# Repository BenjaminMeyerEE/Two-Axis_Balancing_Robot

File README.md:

# Two-Axis Balancing Robot

A robot that balances in pitch and roll. The two axes use different hardware: pitch
runs a brushless motor through a VESC over CAN, roll runs a brushed motor through an
H-bridge on a custom power board. Both close around an STM32G474 and an ICM-42688-P
IMU on a custom carrier board. Two custom 4-layer boards, designed in KiCad.

<!-- TODO
     - mechanical: CAD screenshots once the design is finished
     - the Simulink model and the LQR weight-selection model, once cleaned up
     - fp-lib-table on both boards points at C:/Users/brmey/Downloads, so footprint
       libraries won't resolve on another machine
     - the carrier render uses a Nucleo-64 F401 STEP as a stand-in; same form factor
       as the G474RE but the silkscreen says F411 if you look closely
     images are generated, see docs/regenerate-images.md
-->

## Specifications

| Parameter | Value |
|---|---|
| Axes | Pitch and roll, separate drive hardware |
| Controller | STM32G474RET6 (Nucleo-G474RE on the carrier board) |
| IMU | ICM-42688-P over SPI, both interrupt lines broken out |
| Pitch drive | Brushless motor via VESC, commanded over CAN |
| Pitch feedback | TLE5012 magnetic encoder, SPI to the VESC |
| Roll drive | Brushed motor via TB6612FNG dual H-bridge |
| Roll feedback | Quadrature encoder into the carrier board |
| Battery | 3S LiPo, 11.1 V nominal |
| Carrier board | 101.6 × 92.9 mm, 4-layer |
| Power board | 50.0 × 42.9 mm, 4-layer |

## Status

Both custom PCBs are designed and the electrical architecture is laid out. Mechanical
design is partly finished.

I simulated the pitch axis in Simulink first, and that's what pushed me away from PID
and toward LQR. Wheel position and tilt are coupled through the dynamics, so tuning
them as separate loops meant the two kept fighting each other. Full state feedback
made more sense than trying to manage that interaction by hand.

What I'm working on now is the model itself: deriving the equations of motion with
Lagrangian mechanics, linearizing about the upright equilibrium, and designing a
discrete-time LQR with Bryson's rule setting the cost weights. That work is all in
MATLAB.

## Repository layout

| Path | Contents |
|---|---|
| `hardware/two_axis_balancing_carrier/` | Carrier board KiCad project |
| `hardware/two_axis_balancing_power/` | Power board KiCad project |
| `docs/` | Architecture diagram, board renders, layer plots |

## Hardware

Both boards are 4-layer. Every copper layer below is plotted from the top and
unmirrored, so features line up between layers.

### Carrier board

101.6 × 92.9 mm. Holds the Nucleo-G474RE and everything the control loop reads.

| | |
|---|---|
|  |  |

The ICM-42688-P is on SPI (`CS`, `SCLK`, `SDI`, `SDO`) with `INT1` and `INT2` brought
out, so the loop can run off data-ready rather than polling. An SN65HVD230 with 120 Ω
termination puts the board on the CAN bus to the VESC. A MIC5219-3.3 makes the 3.3 V
rail from the 5 V coming off the power board.

Roll encoder channels come in here on `ENC_A` / `ENC_B`. Motor commands (`AIN1`,
`AIN2`, `PWMA`, `STBY`) and the battery signals go back to the power board over a 2×5
IDC ribbon. There are 13 test points, and the SPI, UART, encoder and rail pads are all
labelled on the silkscreen for bring-up.

| `F.Cu` | `In1.Cu` |
|---|---|
|  |  |

| `In2.Cu` | `B.Cu` |
|---|---|
|  |  |

### Power board

50.0 × 42.9 mm. Takes the battery in and handles everything that touches VBAT.

| | |
|---|---|
|  |  |

Battery comes in on an XT60, behind a 3 A fuse, an AO3401A P-channel MOSFET for
reverse polarity, and a 10 V zener. An RPL-1.0-R module makes the 5 V rail and reports
`Buck_PG` back to the MCU. A TB6612FNG dual H-bridge drives the roll motor on
`MOTOR_P` / `MOTOR_N`.

Battery monitoring is done on this board rather than in firmware. A divider gives
`BAT_LEV`, an LM393 compares it against `BAT_REF`, and `BAT_LOW` goes back to the
carrier board. The MCU sees both the raw level and a latched low flag.

| `F.Cu` | `In1.Cu` |
|---|---|
|  |  |

| `In2.Cu` | `B.Cu` |
|---|---|
|  |  |

### Connectors

| Board | Ref | Connector | Carries |
|---|---|---|---|
| Power | `J1` | XT60 | 3S battery in |
| Power | `J3` | JST XH, 2-pin | Roll motor out (`MOTOR_P` / `MOTOR_N`) |
| Power | `J2` | IDC 2×5 | To the carrier board |
| Carrier | `J5` | IDC 2×5 | To the power board |
| Carrier | `J2` | JST XH, 4-pin | Roll encoder (`ENC_A`, `ENC_B`, 5 V, GND) |
| Carrier | `J1` | JST GH, 3-pin | CAN to the VESC (`CANH`, `CANL`, GND) |

The 2×5 ribbon is the only link between the two boards. It carries the 5 V rail and
ground, the four TB6612FNG control lines (`AIN1`, `AIN2`, `PWMA`, `STBY`) and the two
battery monitoring signals (`BAT_LEV`, `BAT_LOW`). VBAT never reaches the carrier
board, which only ever sees 5 V.

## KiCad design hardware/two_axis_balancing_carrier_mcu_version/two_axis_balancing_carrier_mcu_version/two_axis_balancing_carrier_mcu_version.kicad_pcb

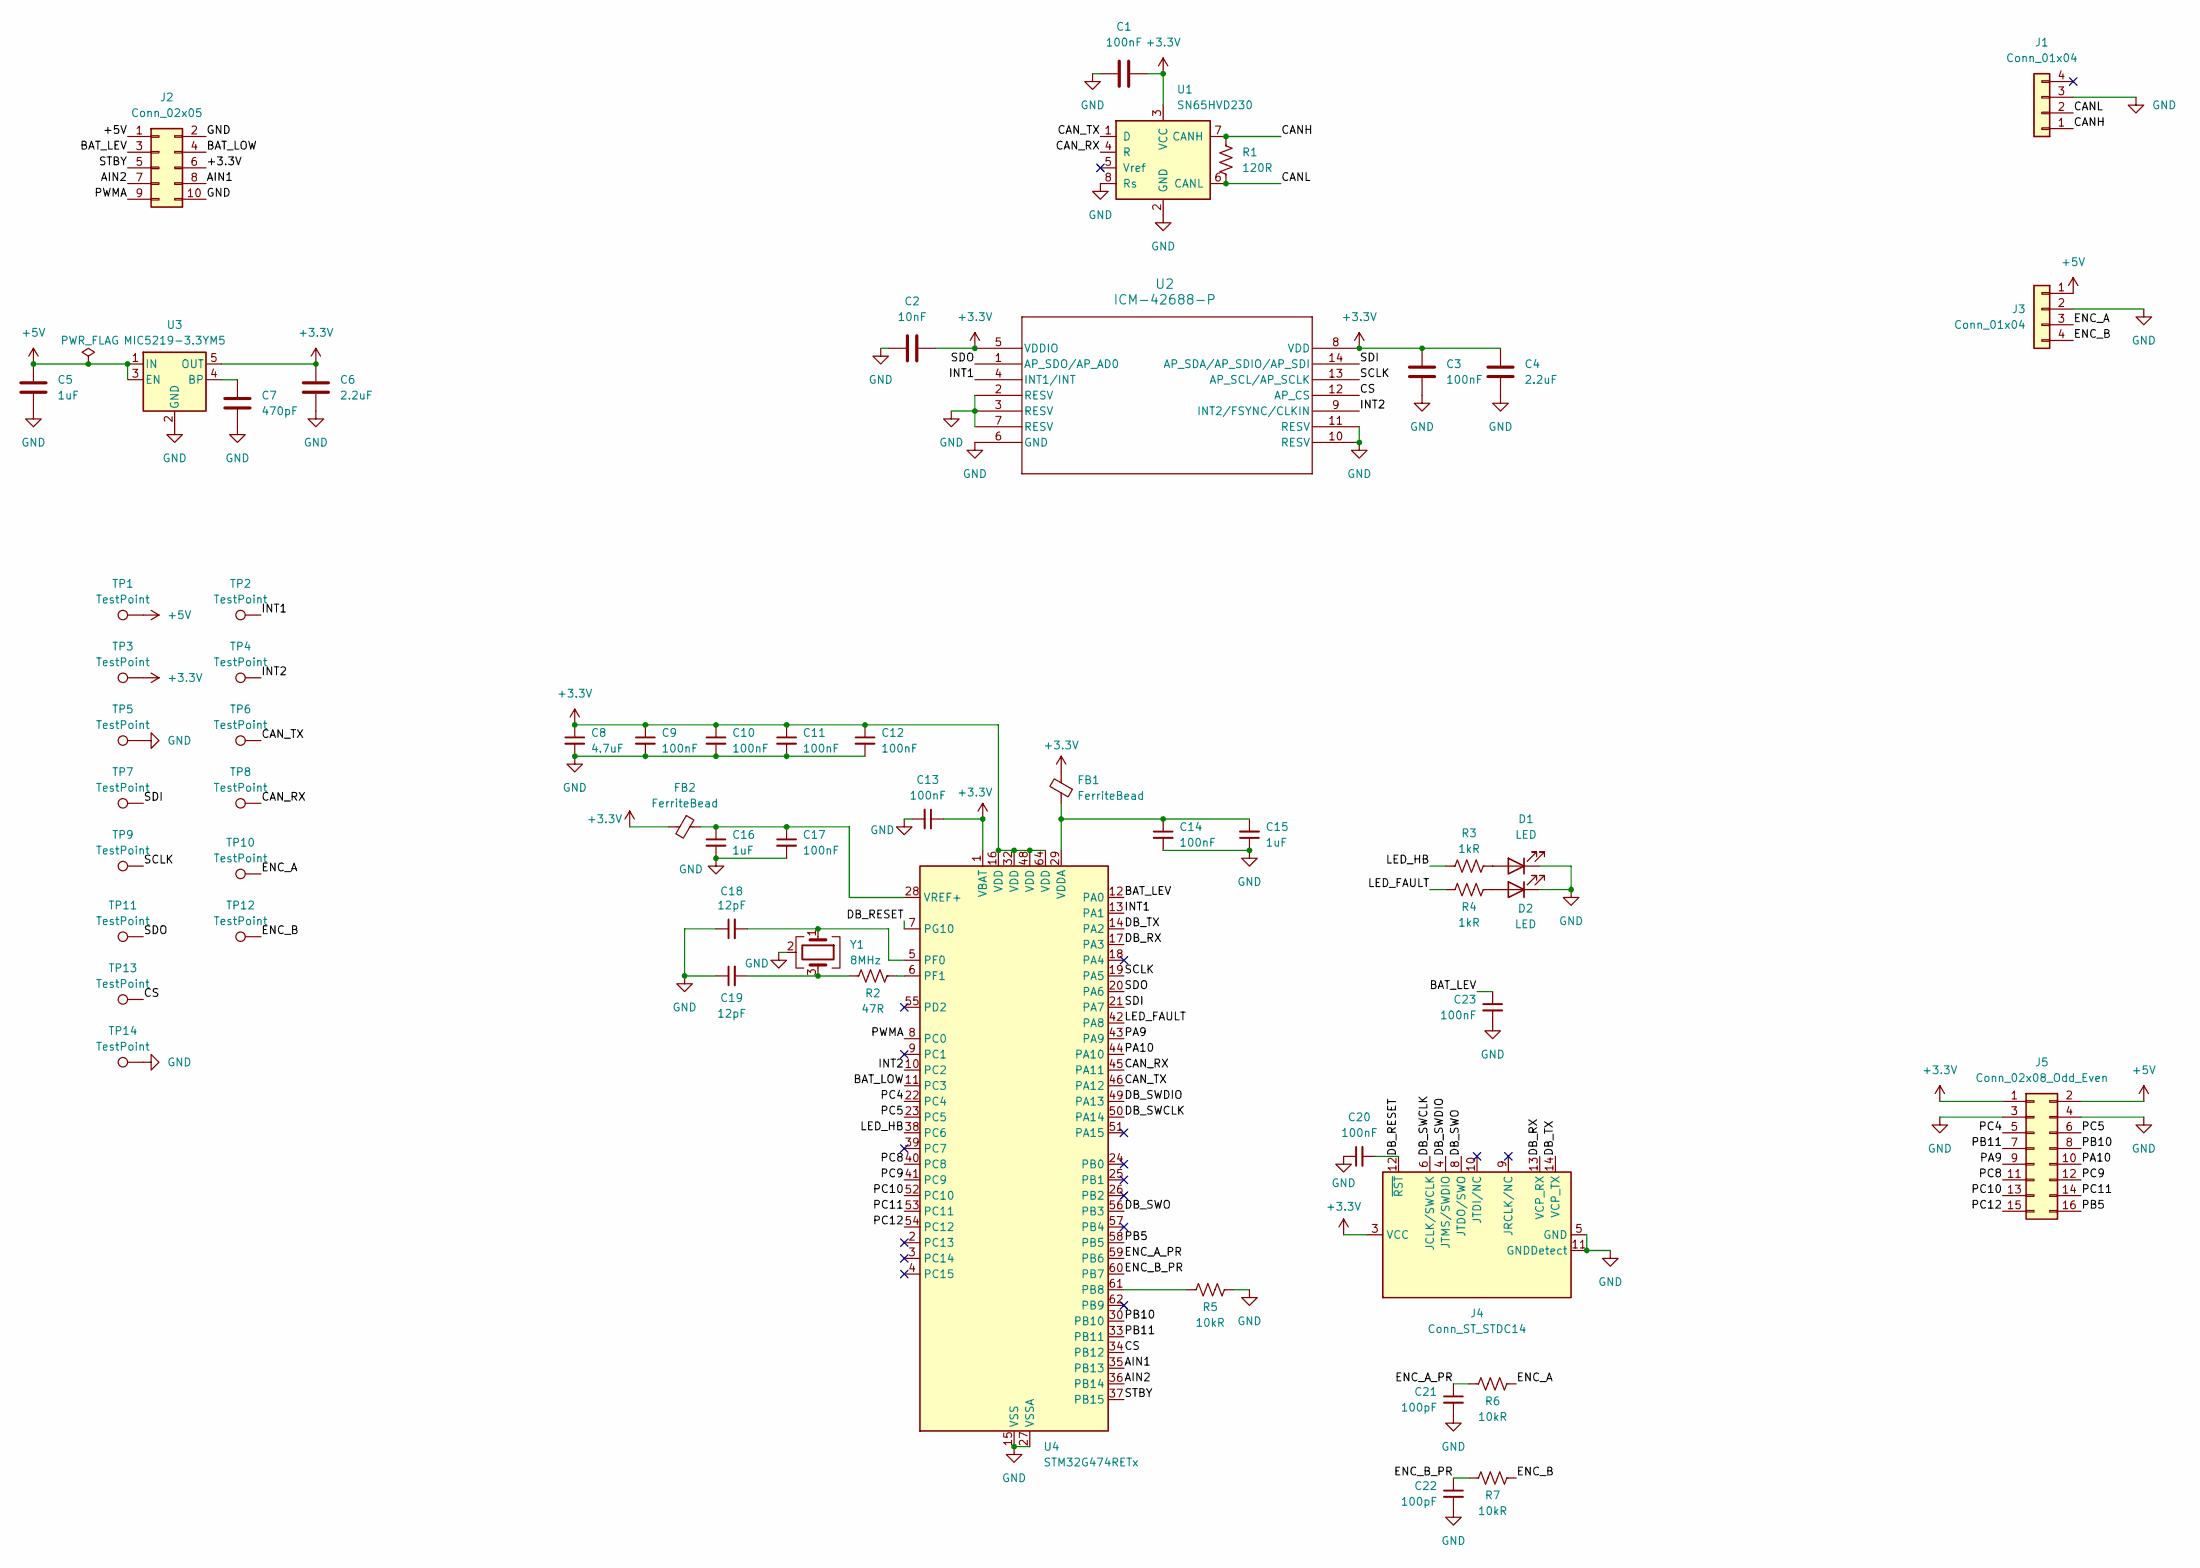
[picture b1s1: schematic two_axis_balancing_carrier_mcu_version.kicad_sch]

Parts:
C1, C3, C9, C10, C11, C12, C13, C14, C17, C20, C23: 100nF; C_0603_1608Metric
C2: 10nF; C_0603_1608Metric
C4, C6: 2.2uF; C_0805_2012Metric
C5: 1uF; C_0603_1608Metric
C7: 470pF; C_0603_1608Metric
C8: 4.7uF; C_0805_2012Metric
C15, C16: 1uF; C_0805_2012Metric
C18, C19: 12pF; C_0603_1608Metric
C21, C22: 100pF; C_0603_1608Metric
D1, D2: LED; LED_0603_1608Metric
FB1, FB2: FerriteBead; C_0603_1608Metric
J1: Conn_01x04; JST_GH_BM04B-GHS-TBT_1x04-1MP_P1.25mm_Vertical
J2: Conn_02x05; IDC-Header_2x05_P2.54mm_Vertical
J3: Conn_01x04; JST_XH_B4B-XH-A_1x04_P2.50mm_Vertical
J4: Conn_ST_STDC14; PinHeader_2x07_P1.27mm_Vertical
J5: Conn_02x08_Odd_Even; PinHeader_2x08_P2.54mm_Vertical
R1: 120R; R_0603_1608Metric
R2: 47R; R_0603_1608Metric
R3, R4: 1kR; R_0603_1608Metric
R5, R6, R7: 10kR; R_0603_1608Metric
TP1, TP2, TP3, TP4, TP6, TP7, TP8, TP9, TP10, TP11, TP12, TP13: TestPoint; TestPoint_Pad_D1.0mm
TP5, TP14: TestPoint; TestPoint_Keystone_5015_Micro_Mini
U1: SN65HVD230; SOIC-8_3.9x4.9mm_P1.27mm
U2: ICM-42688-P; LGA14_2P5X3X0P91_TDK
U3: MIC5219-3.3YM5; SOT-23-5
U4: STM32G474RETx; LQFP-64_10x10mm_P0.5mm
Y1: 8MHz; Crystal_SMD_3225-4Pin_3.2x2.5mm

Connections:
+3.3V: C1.1, C2.2, C3.1, C4.1, C6.1, C8.1, C9.1, C10.1, C11.1, C12.1, C13.1, FB1.2, FB2.2, J2.6, J4.3 (VCC), J5.1, TP3.1 (1_1), U1.3 (VCC), U2.5 (VDDIO), U2.8 (VDD), U3.5 (OUT), U4.1 (VBAT), U4.16 (VDD), U4.32 (VDD), U4.48 (VDD), U4.64 (VDD)
+5V: C5.1, J2.1, J3.1, J5.2, TP1.1 (1_1), U3.1 (IN), U3.3 (EN)
/AIN1: J2.8, U4.35 (PB13)
/AIN2: J2.7, U4.36 (PB14)
/BAT_LEV: C23.1, J2.3, U4.12 (PA0)
/BAT_LOW: J2.4, U4.11 (PC3)
/CANH: J1.1, R1.1, U1.7 (CANH)
/CANL: J1.2, R1.2, U1.6 (CANL)
/CAN_RX: TP8.1 (1_1), U1.4 (R), U4.45 (PA11)
/CAN_TX: TP6.1 (1_1), U1.1 (D), U4.46 (PA12)
/CS: TP13.1 (1_1), U2.12 (AP_CS), U4.34 (PB12)
/DB_RESET: C20.2, J4.12 (~RST), U4.7 (PG10)
/DB_RX: J4.13 (VCP_RX), U4.17 (PA3)
/DB_SWCLK: J4.6 (JCLK/SWCLK), U4.50 (PA14)
/DB_SWDIO: J4.4 (JTMS/SWDIO), U4.49 (PA13)
/DB_SWO: J4.8 (JTDO/SWO), U4.56 (PB3)
/DB_TX: J4.14 (VCP_TX), U4.14 (PA2)
/ENC_A: J3.3, R6.2, TP10.1 (1_1)
/ENC_A_PR: C21.1, R6.1, U4.59 (PB6)
/ENC_B: J3.4, R7.2, TP12.1 (1_1)
/ENC_B_PR: C22.1, R7.1, U4.60 (PB7)
/INT1: TP2.1 (1_1), U2.4 (INT1/INT), U4.13 (PA1)
/INT2: TP4.1 (1_1), U2.9 (INT2/FSYNC/CLKIN), U4.10 (PC2)
/LED_FAULT: R4.1, U4.42 (PA8)
/LED_HB: R3.1, U4.38 (PC6)
/PA9: J5.9, U4.43 (PA9)
/PA10: J5.10, U4.44 (PA10)
/PB5: J5.16, U4.58 (PB5)
/PB10: J5.8, U4.30 (PB10)
/PB11: J5.7, U4.33 (PB11)
/PC4: J5.5, U4.22 (PC4)
/PC5: J5.6, U4.23 (PC5)
/PC8: J5.11, U4.40 (PC8)
/PC9: J5.12, U4.41 (PC9)
/PC10: J5.13, U4.52 (PC10)
/PC11: J5.14, U4.53 (PC11)
/PC12: J5.15, U4.54 (PC12)
/PWMA: J2.9, U4.8 (PC0)
/SCLK: TP9.1 (1_1), U2.13 (AP_SCL/AP_SCLK), U4.19 (PA5)
/SDI: TP7.1 (1_1), U2.14 (AP_SDA/AP_SDIO/AP_SDI), U4.21 (PA7)
/SDO: TP11.1 (1_1), U2.1 (AP_SDO/AP_AD0), U4.20 (PA6)
/STBY: J2.5, U4.37 (PB15)
GND: C1.2, C2.1, C3.2, C4.2, C5.2, C6.2, C7.2, C8.2, C9.2, C10.2, C11.2, C12.2, C13.2, C14.2, C15.1, C16.2, C17.2, C18.1, C19.1, C20.1, C21.2, C22.2, C23.2, D1.1 (K), D2.1 (K), J1.3, J2.2, J2.10, J3.2, J4.5 (GND), J4.7 (GND), J4.11 (GNDDetect), J5.3, J5.4, R5.2, TP5.1 (1_1), TP14.1 (1_1), U1.2 (GND), U1.8 (Rs), U2.2 (RESV), U2.3 (RESV), U2.6 (GND), U2.7 (RESV), U2.10 (RESV), U2.11 (RESV), U3.2 (GND), U4.15 (VSS), U4.27 (VSSA), U4.31 (VSS), U4.47 (VSS), U4.63 (VSS), Y1.2 (G), Y1.4 (G)
unnamed: C19.2, R2.1, Y1.3
unnamed: D1.2 (A), R3.2
unnamed: D2.2 (A), R4.2
unnamed: C7.1, U3.4 (BP)
unnamed: R5.1, U4.61 (PB8)
unnamed: C18.2, U4.5 (PF0), Y1.1
unnamed: R2.2, U4.6 (PF1)
unnamed: C14.1, C15.2, FB1.1, U4.29 (VDDA)
unnamed: C16.1, C17.1, FB2.1, U4.28 (VREF+)

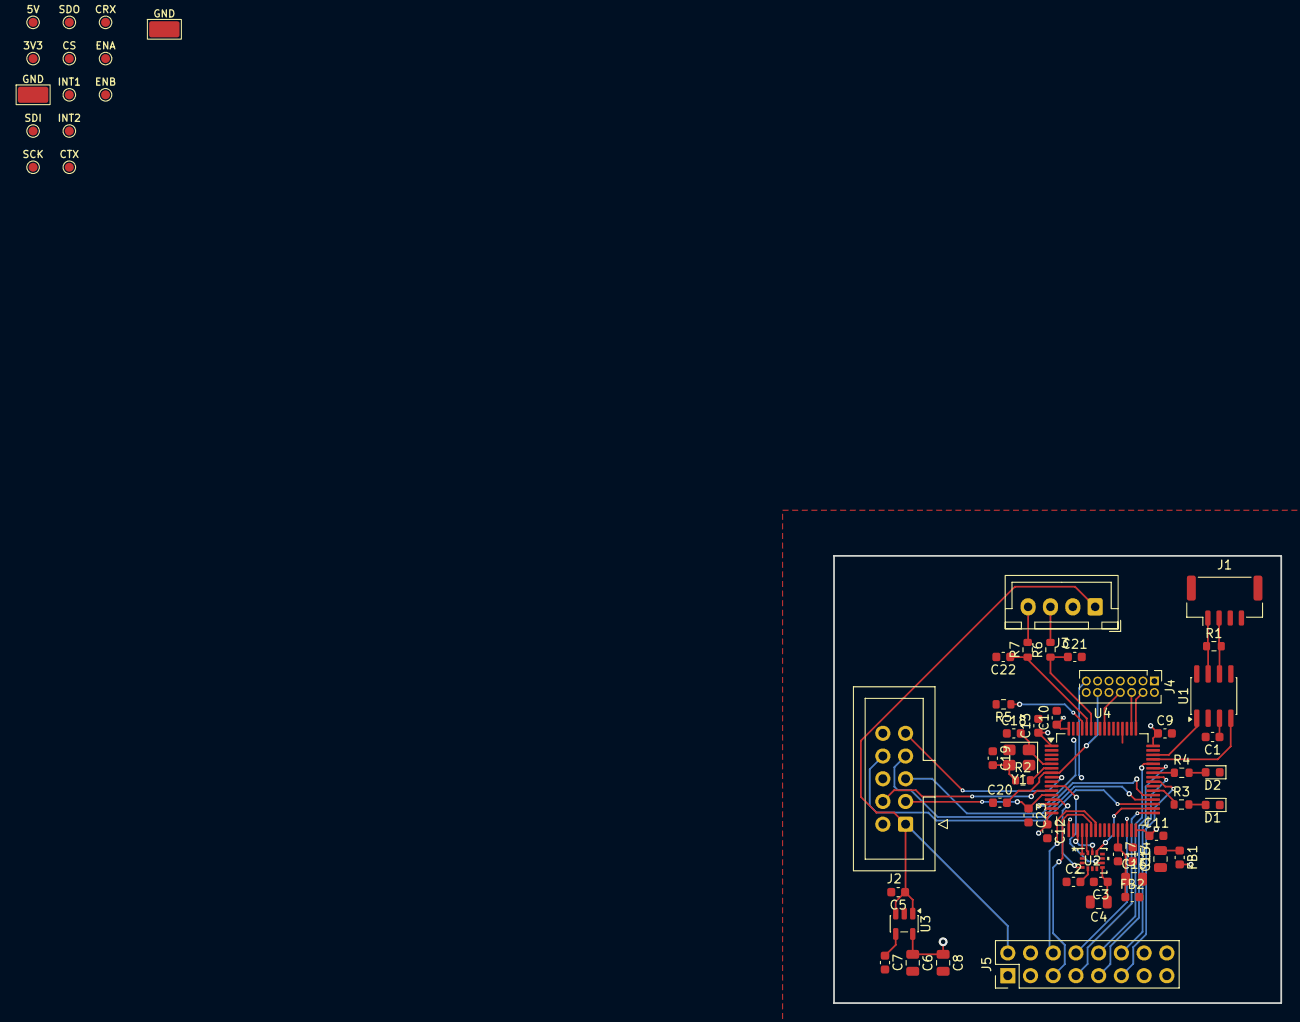
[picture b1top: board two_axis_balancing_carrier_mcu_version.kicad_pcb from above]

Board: 4 copper layers, 50.0 x 50.0 mm, 58 parts (0 on the bottom side), 52 nets.

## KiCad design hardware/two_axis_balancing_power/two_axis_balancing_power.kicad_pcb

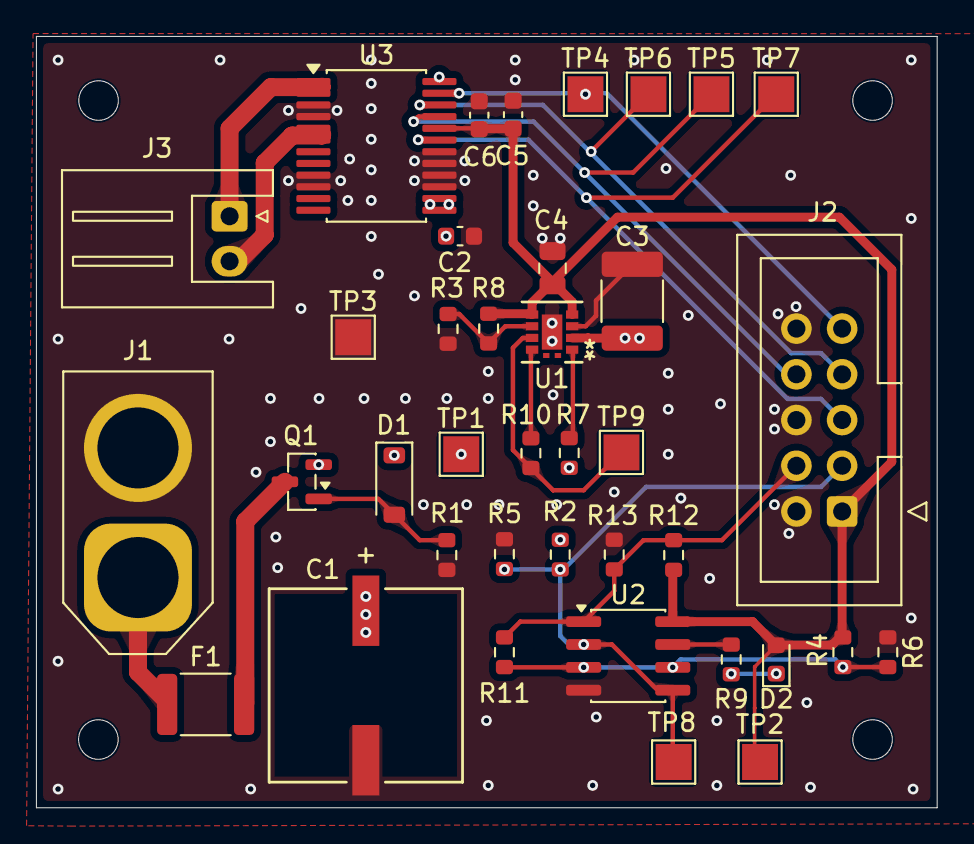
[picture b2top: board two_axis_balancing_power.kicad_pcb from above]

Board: 4 copper layers, 50.0 x 42.9 mm, 38 parts (0 on the bottom side), 21 nets.

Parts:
C1: 470uF; PCAP_10x10-ELECT_NCA
C2, C6: 100nF; C_0603_1608Metric
C3: 20uF; C_1812_4532Metric
C4: 22uF; C_0805_2012Metric
C5: 10uF; C_0603_1608Metric
D1: 10V; D_SOD-123
D2: LED; LED_0603_1608Metric
F1: 3A; Fuse_1812_4532Metric
J1: Conn_01x02; AMASS_XT60-M_1x02_P7.20mm_Vertical
J2: Conn_02x05; IDC-Header_2x05_P2.54mm_Vertical
J3: Conn_01x02; JST_XH_S2B-XH-A_1x02_P2.50mm_Horizontal
Q1: AO3401A; SOT-23
R1, R4, R5, R12: 10kR; R_0603_1608Metric
R2: 47kR; R_0603_1608Metric
R3, R11: 220kR; R_0603_1608Metric
R6: 5.9kR; R_0603_1608Metric
R7, R10: 100kR; R_0603_1608Metric
R8: 1613kR; R_0603_1608Metric
R9: 470R; R_0603_1608Metric
R13: 15kR; R_0603_1608Metric
TP1, TP2, TP3, TP4, TP5, TP6, TP7, TP8, TP9: TestPoint; TestPoint_Pad_2.0x2.0mm
U1: RPL-1.0-R; 11L-LGA-M_RPL-1_RCP
U2: LM393; SOIC-8_3.9x4.9mm_P1.27mm
U3: TB6612FNG; SSOP-24_5.3x8.2mm_P0.65mm

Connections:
+5V: C4.2, C5.2, C6.2, D2.2 (A), J2.1, R4.1, R8.2, R12.1, TP2.1 (1_1), U1.4 (VOUT), U1.5 (VOUT), U2.8 (V+), U3.20 (VCC)
/AIN1: J2.8, TP5.1 (1_1), U3.21 (AIN1)
/AIN2: J2.7, TP6.1 (1_1), U3.22 (AIN2)
/BAT_LEV: J2.3, R2.1, R5.2, TP8.1 (1_1), U2.2 (-), U2.5 (+)
/BAT_LOW: J2.4, R11.1, R12.2, R13.1, U2.1
/Buck_PG: R10.2, TP9.1 (1_1), U1.7 (PG)
/MOTOR_N: J3.2, U3.5 (AO2), U3.6 (AO2)
/MOTOR_P: J3.1, U3.1 (AO1), U3.2 (AO1)
/PWMA: J2.9, TP4.1 (1_1), U3.23 (PWMA)
/STBY: J2.5, TP7.1 (1_1), U3.19 (STBY)
GND: C1.2, C2.2, C3.1, C4.1, C5.1, C6.1, J1.2, J2.2, J2.6, J2.10, R1.2, R3.1, R5.1, R6.2, R13.2, TP3.1 (1_1), U1.3 (PGND), U1.11 (TP), U2.4 (V-), U3.3 (PGND1), U3.4 (PGND1), U3.9 (PGND2), U3.10 (PGND2), U3.15 (PWMB), U3.16 (BIN2), U3.17 (BIN1), U3.18 (GND)
unnamed: D1.2 (A), Q1.1 (G), R1.1
unnamed: D2.1 (K), R9.1
unnamed: F1.1, J1.1
unnamed: F1.2, Q1.3 (D)
unnamed: R9.2, U2.7
unnamed: R7.2, U1.1 (CTRL)
unnamed: R3.2, R8.1, U1.6 (FB)
unnamed: R10.1, U1.8 (VCC)
unnamed: R4.2, R6.1, R11.2, U2.3 (+), U2.6 (-)
VBAT: C1.1, C2.1, C3.2, D1.1 (K), Q1.2 (S), R2.2, R7.1, TP1.1 (1_1), U1.2 (VIN), U3.13 (VM2), U3.14 (VM3), U3.24 (VM1)

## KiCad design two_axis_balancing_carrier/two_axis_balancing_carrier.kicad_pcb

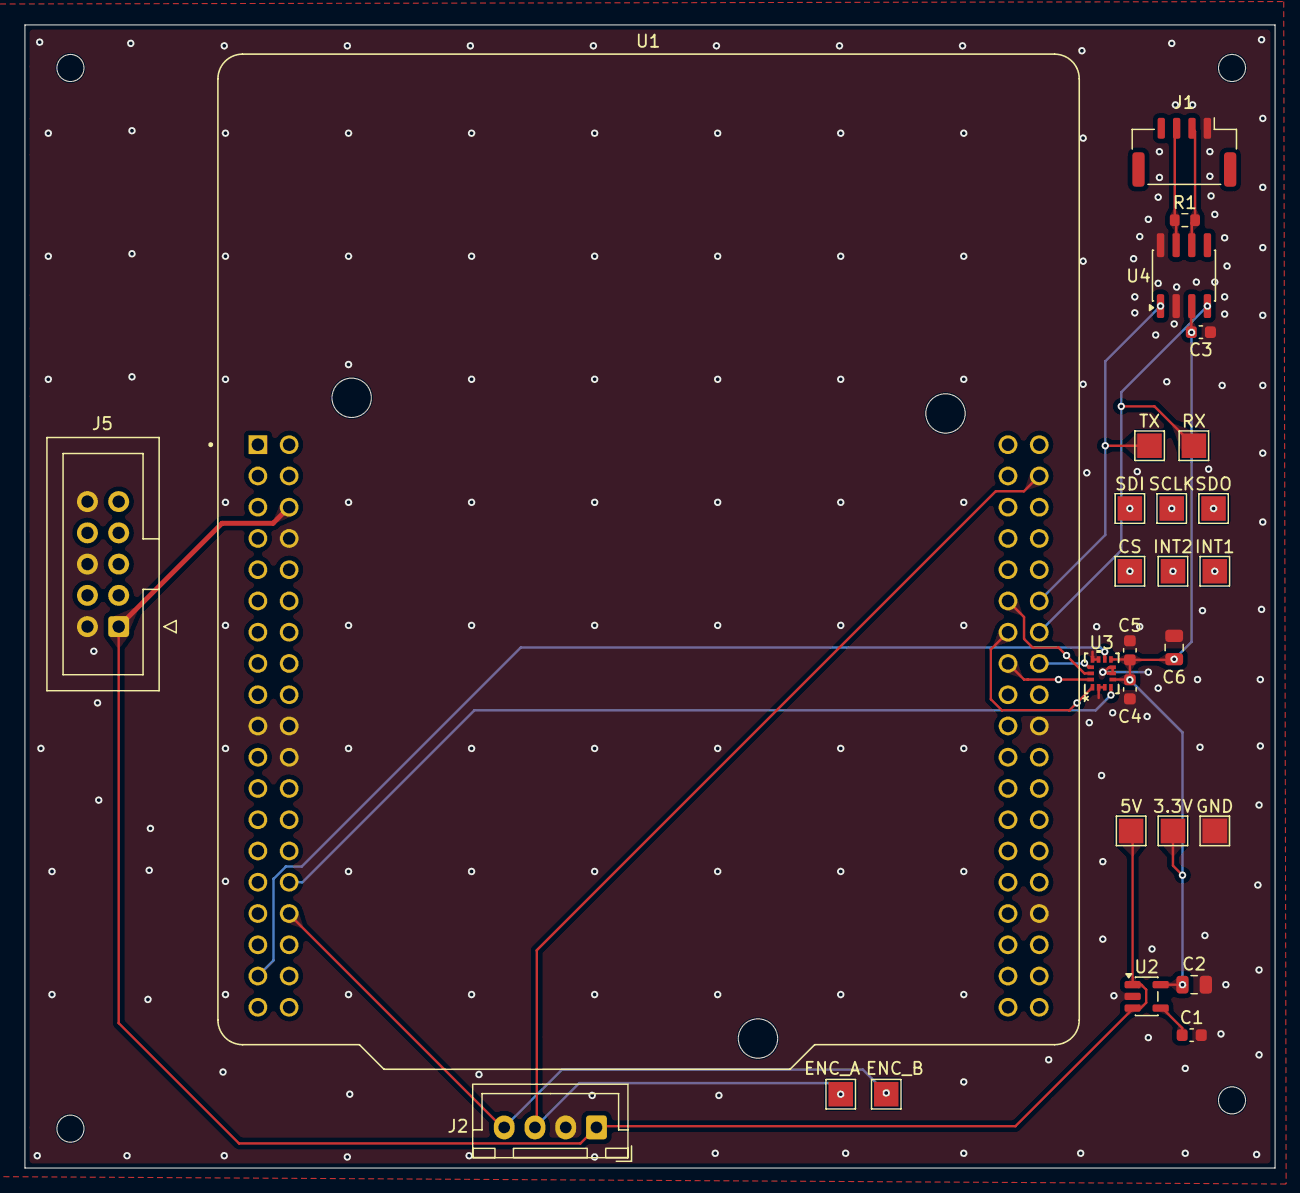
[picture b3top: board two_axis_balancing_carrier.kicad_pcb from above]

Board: 4 copper layers, 101.6 x 92.9 mm, 27 parts (0 on the bottom side), 22 nets.

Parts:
3.3V, 5V: TestPoint; TestPoint_Pad_2.0x2.0mm
C1: 470pF; C_0603_1608Metric
C2, C6: 2.2uF; C_0805_2012Metric
C3, C5: 100nF; C_0603_1608Metric
C4: 10nF; C_0603_1608Metric
CS: TestPoint; TestPoint_Pad_2.0x2.0mm
ENC_A: TestPoint; TestPoint_Pad_2.0x2.0mm
ENC_B: TestPoint; TestPoint_Pad_2.0x2.0mm
GND: TestPoint; TestPoint_Pad_2.0x2.0mm
INT1, INT2: TestPoint; TestPoint_Pad_2.0x2.0mm
J1: Conn_01x03; JST_GH_BM04B-GHS-TBT_1x04-1MP_P1.25mm_Vertical
J2: Conn_01x04; JST_XH_B4B-XH-A_1x04_P2.50mm_Vertical
J5: Conn_02x05; IDC-Header_2x05_P2.54mm_Vertical
R1: 120R; R_0603_1608Metric
RX: TestPoint; TestPoint_Pad_2.0x2.0mm
SCLK: TestPoint; TestPoint_Pad_2.0x2.0mm
SDI: TestPoint; TestPoint_Pad_2.0x2.0mm
SDO: TestPoint; TestPoint_Pad_2.0x2.0mm
TX: TestPoint; TestPoint_Pad_2.0x2.0mm
U1: NUCLEO-G474RE; MODULE_NUCLEO-G474RE
U2: MIC5219-3.3YM5; SOT-23-5
U3: ICM-42688-P; LGA14_2P5X3X0P91_TDK
U4: SN65HVD230; SOIC-8_3.9x4.9mm_P1.27mm

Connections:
+3.3V: 3.3V.1 (1_1), C2.1, C3.1, C4.2, C5.1, C6.1, U2.5 (OUT), U3.5 (VDDIO), U3.8 (VDD), U4.3 (VCC)
+5V: 5V.1 (1_1), J2.1, J5.1, U1.CN7_6 (E5V), U2.1 (IN), U2.3 (EN)
/AIN1: J5.8, U1.CN7_23 (PC13)
/AIN2: J5.7, U1.CN7_25 (PC14)
/BAT_LEV: J5.3, U1.CN7_28 (PA0)
/BAT_LOW: J5.4, U1.CN7_37 (PC3)
/CANH: J1.3, R1.1, U4.7 (CANH)
/CANL: J1.2, R1.2, U4.6 (CANL)
/CS: CS.1 (1_1), U1.CN10_16 (PB12), U3.12 (AP_CS)
/ENC_A: ENC_A.1 (1_1), J2.3, U1.CN10_4 (PC6)
/ENC_B: ENC_B.1 (1_1), J2.4, U1.CN7_32 (PA4)
/INT1: INT1.1 (1_1), U1.CN7_30 (PA1), U3.4 (INT1/INT)
/INT2: INT2.1 (1_1), U1.CN7_35 (PC2), U3.9 (INT2/FSYNC/CLKIN)
/PWMA: J5.9, U1.CN7_38 (PC0/PA15)
/RX: RX.1 (1_1), U1.CN10_14 (PA11), U4.4 (R)
/SCLK: SCLK.1 (1_1), U1.CN10_11 (PA5), U3.13 (AP_SCL/AP_SCLK)
/SDI: SDI.1 (1_1), U1.CN10_15 (PA7), U3.14 (AP_SDA/AP_SDIO/AP_SDI)
/SDO: SDO.1 (1_1), U1.CN10_13 (PA6), U3.1 (AP_SDO/AP_AD0)
/STBY: J5.5, U1.CN7_27 (PC15)
/TX: TX.1 (1_1), U1.CN10_12 (PA12), U4.1 (D)
GND: C1.2, C2.2, C3.2, C4.1, C5.2, C6.2, GND.1 (1_1), J1.1, J2.2, J5.2, J5.6, J5.10, U1.CN7_8 (GND_CN7_8), U1.CN7_19 (GND_CN7_19), U1.CN7_20 (GND_CN7_20), U1.CN7_22 (GND_CN7_22), U1.CN10_20 (GND_CN10_20), U1.CN10_32 (AGND), U2.2 (GND), U3.2 (RESV), U3.3 (RESV), U3.6 (GND), U3.7 (RESV), U3.10 (RESV), U3.11 (RESV), U4.2 (GND), U4.8 (Rs)
unnamed: C1.1, U2.4 (BP)

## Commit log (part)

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2026-06-01 Two-axis balancing robot: carrier and power boards
2026-06-01 Fixed file structure
2026-06-02 Power board topology finished and carrier board started
2026-06-02 Finished topology
2026-06-08 Sized passives
2026-06-09 Started pcb design
2026-06-17 Almost finished pcb
2026-06-17 Finished pcb
2026-06-18 Carrier schematic finished and power board polished
2026-06-19 Power actually finished; carrier pcb started
2026-06-27 Carrier layout finished
